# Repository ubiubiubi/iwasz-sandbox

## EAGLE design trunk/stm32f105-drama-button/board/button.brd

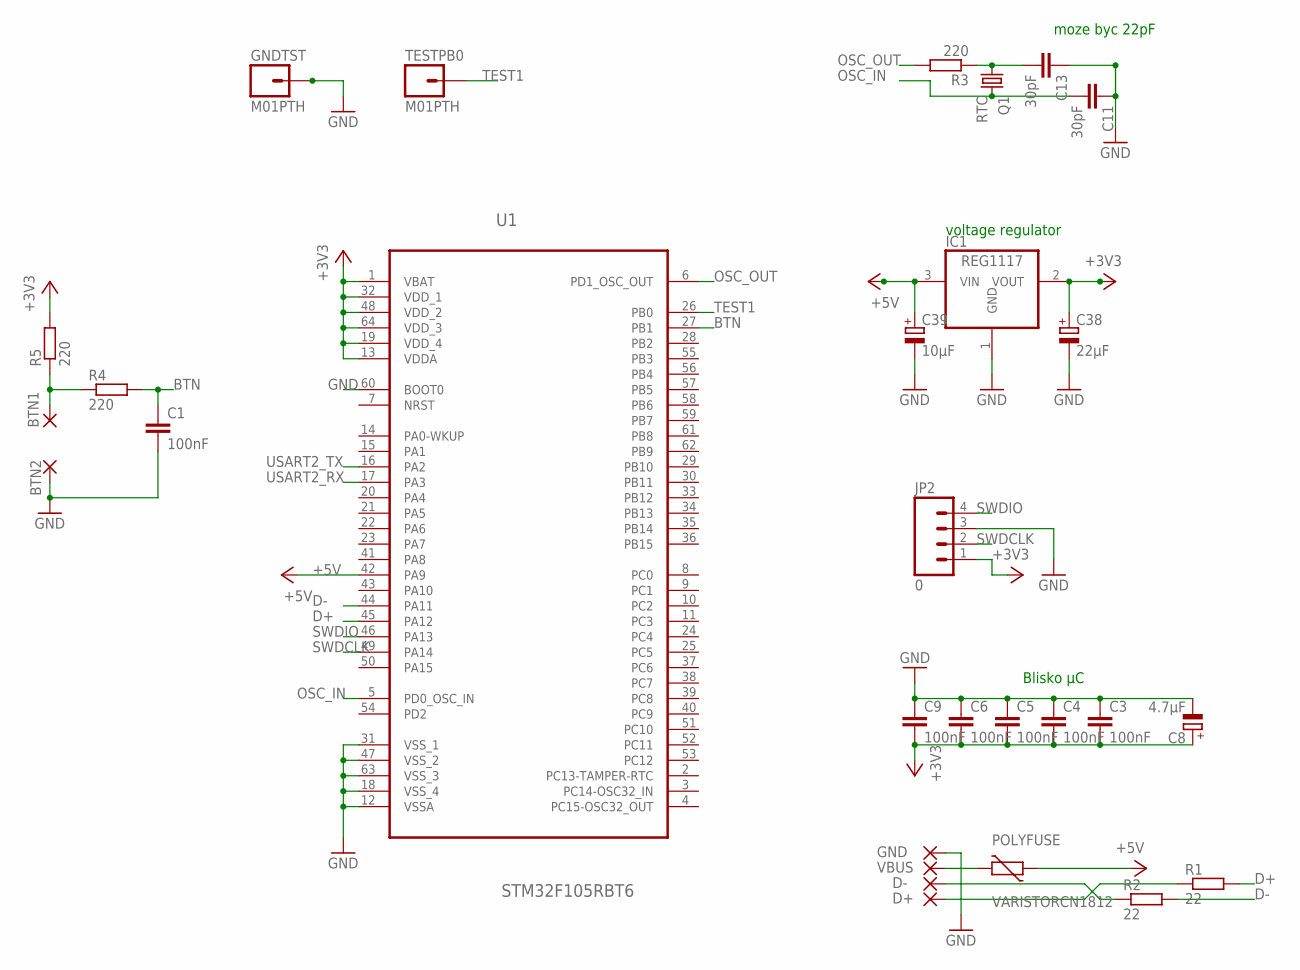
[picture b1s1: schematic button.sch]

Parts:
BTN1, BTN2: 1,6/0,8
C1, C3, C4, C5, C6, C9: 100nF; C0603
C8: 4.7µF; A/3216-18R
C11, C13: 30pF; C0603
C38: 22µF; B/3528-21W
C39: 10µF; B/3528-21W
D+: 1,6/0,8
D-: 1,6/0,8
GND: 1,6/0,8
GNDTST: M01PTH; 1X01
IC1: REG1117; SOT223
JP2: 0; 1X04
POLYFUSE: VARISTORCN1812; CT/CN1812
Q1: RTC; HC49/S
R1, R2: 22; R0805
R3, R4, R5: 220; R0603
TESTPB0: M01PTH; 1X01
U1: STM32F105RBT6; QFP50P1200X1200X160-64N
VBUS: 1,6/0,8

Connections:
+3V3: C3.2, C4.2, C5.2, C6.2, C8.+, C9.2, C38.+, IC1.2 (VOUT), JP2.1, R5.2, U1.1 (VBAT), U1.13 (VDDA), U1.19 (VDD_4), U1.32 (VDD_1), U1.48 (VDD_2), U1.64 (VDD_3)
+5V: C39.+, IC1.3 (VIN), POLYFUSE.1, U1.42 (PA9)
BTN: C1.1, R4.2, U1.27 (PB1)
D+: R1.2, U1.45 (PA12)
D-: R2.2, U1.44 (PA11)
GND: BTN2.1, C1.2, C3.1, C4.1, C5.1, C6.1, C8.-, C9.1, C11.1, C13.1, C38.-, C39.-, GND.1, GNDTST.1, IC1.1 (GND), JP2.3, U1.12 (VSSA), U1.18 (VSS_4), U1.31 (VSS_1), U1.47 (VSS_2), U1.60 (BOOT0), U1.63 (VSS_3)
unnamed: C13.2, Q1.1, R3.1
unnamed: BTN1.1, R4.1, R5.1
unnamed: D+.1, R1.1
unnamed: D-.1, R2.1
unnamed: POLYFUSE.2, VBUS.1
OSC_IN: C11.2, Q1.2, U1.5 (PD0_OSC_IN)
OSC_OUT: R3.2, U1.6 (PD1_OSC_OUT)
SWDCLK: JP2.2, U1.49 (PA14)
SWDIO: JP2.4, U1.46 (PA13)
TEST1: TESTPB0.1, U1.26 (PB0)
USART2_RX: U1.17 (PA3)
USART2_TX: U1.16 (PA2)

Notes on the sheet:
voltage regulator
Blisko µC
moze byc 22pF

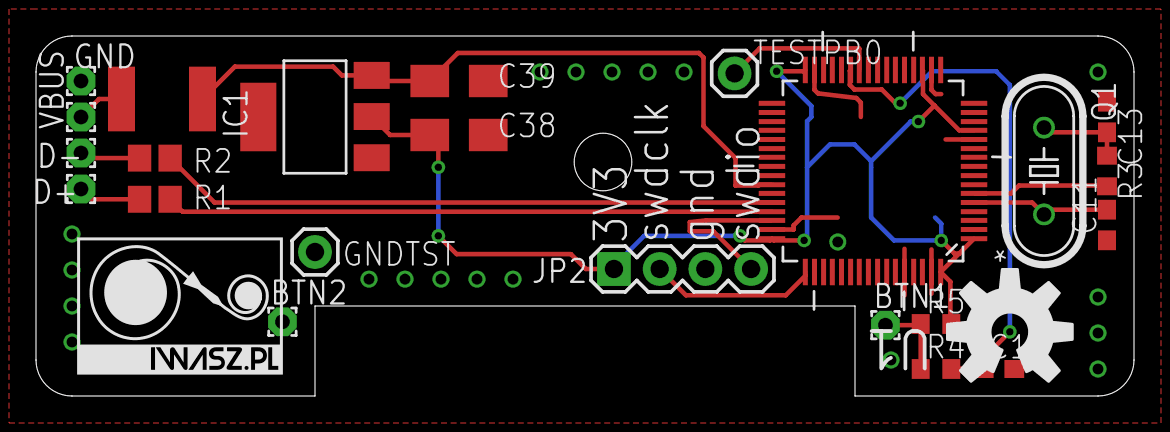
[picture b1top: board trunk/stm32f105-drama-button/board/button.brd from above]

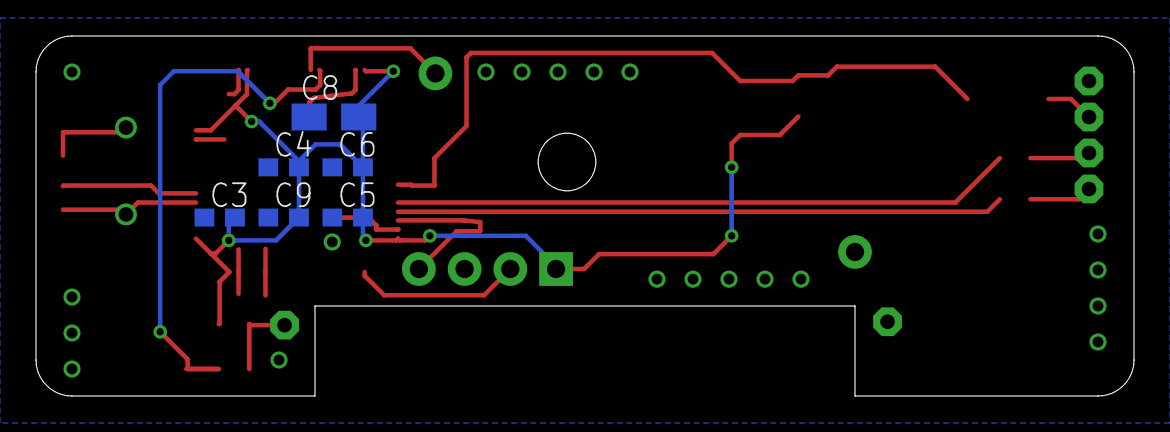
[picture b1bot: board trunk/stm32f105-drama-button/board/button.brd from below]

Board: 2 copper layers, 61.0 x 20.0 mm, 31 parts (6 on the bottom side), 16 nets.

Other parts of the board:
U$1: LOGO-TINY
U$4: OSHW-LOGO-L

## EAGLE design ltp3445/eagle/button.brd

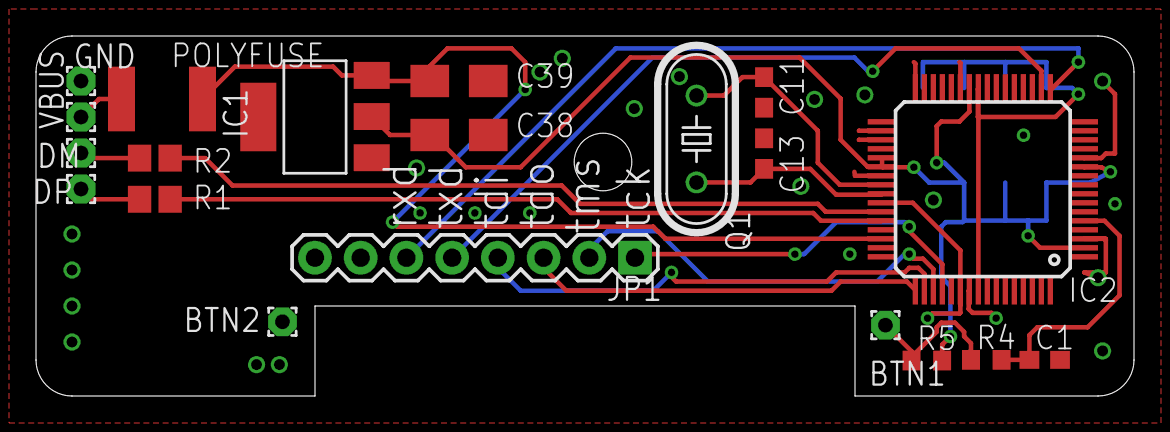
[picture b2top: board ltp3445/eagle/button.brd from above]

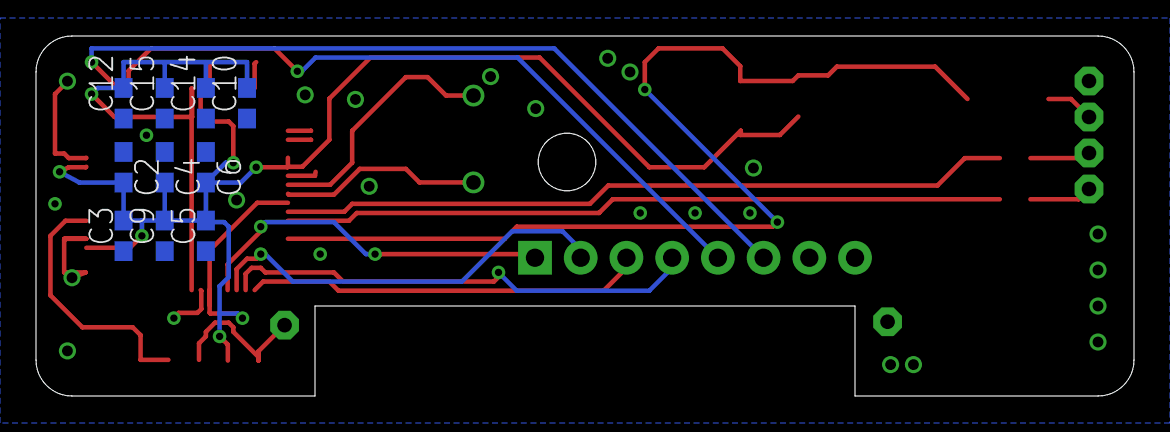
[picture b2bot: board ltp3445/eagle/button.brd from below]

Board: 2 copper layers, 61.0 x 20.0 mm, 30 parts (10 on the bottom side), 19 nets.

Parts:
BTN1, BTN2: 1,6/0,8
C1, C4, C6, C14, C15: 100nF; C0603
C2, C12: 1µF; C0603
C3, C5, C9: 10nF; C0603
C10: 2.2µF; C0603
C11, C13: 10pF; C0603
C38: 22µF; B/3528-21W
C39: 10µF; B/3528-21W
DM: 1,6/0,8
DP: 1,6/0,8
GND: 1,6/0,8
IC1: REG1117; SOT223
IC2: TM4C123[7,G]XXPM; PM_S-PQFP-G64
JP1: 1X08
POLYFUSE: VARISTORCN1812; CT/CN1812
Q1: RTC; HC49/S
R1, R2: 22; R0805
R4, R5: 220; R0603
VBUS: 5V; 1,6/0,8

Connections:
+3V3: C2.2, C3.2, C4.2, C5.2, C6.2, C9.2, C38.+, IC1.2, IC2.2, IC2.11, IC2.26, IC2.37, IC2.38, IC2.42, IC2.54, R5.2
+5V: C39.+, IC1.3, IC2.46, POLYFUSE.1
BTN: C1.1, IC2.5, R4.2
D+: IC2.44, R1.2
D-: IC2.43, R2.2
GND: BTN2.1, C1.2, C2.1, C3.1, C4.1, C5.1, C6.1, C9.1, C10.1, C11.1, C12.1, C13.1, C14.1, C15.1, C38.-, C39.-, GND.1, IC1.1, IC2.3, IC2.12, IC2.27, IC2.32, IC2.34, IC2.35, IC2.39, IC2.55, JP1.7, JP1.8
unnamed: BTN1.1, R4.1, R5.1
unnamed: DP.1, R1.1
unnamed: DM.1, R2.1
unnamed: POLYFUSE.2, VBUS.1
OSC0: C11.2, IC2.40, Q1.2
OSC1: C13.2, IC2.41, Q1.1
RXD: IC2.17, JP1.6
TCK: IC2.52, JP1.1
TDI: IC2.50, JP1.4
TDO: IC2.49, JP1.3
TMS: IC2.51, JP1.2
TXD: IC2.18, JP1.5
VDDC: C10.2, C12.2, C14.2, C15.2, IC2.25, IC2.56

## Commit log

2013-05-27 fgdyhhgn
2013-06-11 Share project "raspberry-first" into "https://iwasz-sandbox.googlecode.com/svn"
2013-06-11 first
2013-07-03 Share project "test05-hello-concurrency" into "https://iwasz-sandbox.googlecode.com/svn"
2013-07-03 hello concurrency
2013-07-21 Share project "blinky" into "https://iwasz-sandbox.googlecode.com/svn"
2013-07-21 Share project "stm32-cmake-test" into "https://iwasz-sandbox.googlecode.com/svn"
2013-07-21 test mediwaiki formatting
2013-08-02 Share project "stm32-test2" into "https://iwasz-sandbox.googlecode.com/svn"
2013-09-10 Share project "i2c-test" into "https://iwasz-sandbox.googlecode.com/svn"
2013-09-13 move
2013-09-13 trash
2013-09-17 I²C, USART, NewLib and gyro connected to I²C works. Nice output in minicom.
2013-09-27 test usb
2013-09-27 3rdparty libraries added. Those are : stdperiph, usbdev, usbhost, usbotg and CMSIS
2013-09-27 Cleared, prepared for further development
2013-09-27 Ignores and USART cfg for printf - still clear and waiting
2013-09-27 usb_conf.h added
2013-10-01 usb_bsp.c added
2013-10-01 usbd_conf.h added
2013-10-01 Few files added
2013-10-01 Libraries updated
2013-10-01 /stm32fxxx_it.c added
2013-10-01 src/system_stm32f4xx.c configured (in fact it was copied from Demonstration app) and that was finally it. This modification made app work.
2013-10-02 Code documentation imporved
2013-10-03 Documentation improvements
2013-10-04 New project USB vendor specific class test
2013-10-04 Documentation ignorea and my vendor specific class. The beginning.
2013-10-05 New project
2013-10-05 Configuration
2013-10-05 WIP sketch of USB driver program
2013-10-09 WIP - not working at the moment
2013-10-10 New interface added
2013-10-10 At last! This freaking isochronous transfer works. Alleluja
2013-10-10 adfsd
2013-10-11 rollback of last changes. Those changes were ported to usb-vendor-specific project
2013-10-13 Tests
2013-10-17 NVIC + EXTI wip
2013-10-18 Little success
2013-10-23 32 inputs
2013-10-24 UI changes
2013-11-06 Isochronous transfers changed to interrupt due to uncertanity that STM32-USB-OTG can handle isochronous at all. Probably a bug in the lib. Changed quadrature signal counting
2013-11-06 Layout improvements
2013-12-17 https://iwasz-sandbox.googlecode.com/svn/trunk/stm32-sdio-tests init
2013-12-29 Project initial commit
2013-12-30 Cleanup
2013-12-30 Device (keyboard) recognized by system. No keypress though
2014-01-01 Keypress A working
2014-01-02 Repository name change
2014-01-02 Drama button for stmf105
2014-01-02 Changin µC to F105
2014-01-02 Porting from F407 to F105
2014-01-05 Play pause implementred instead of dummy "a" button
2014-01-05 New CMSIS added. Status : messed up. Not usable :( The device resets few times, then dies
2014-01-05 Board schematics added
2014-01-06 USART1 broken, but SDIO seems to work
2014-01-06 Fixed quadrature encoding bug. Added LED status
2014-01-06 Set to zero added and negative numbers added
2014-01-06 Set to zero added (control transfer request)
2014-01-07 Theme
2014-01-07 USART still not working
2014-01-08 Tried to fix transfer stall
2014-01-10 It works.
2014-01-10 After few bugs finally I got it working.
2014-01-11 Initial commit, a test project
2014-01-12 Wrote forst test, but it didn\t work
2014-01-12 Initial release
2014-01-13 DMA OK, two transfers
2014-01-20 DB access
2014-03-15 New project test css + gtk loader program
2014-04-18 Share project "tiva-usb-test" into "https://iwasz-sandbox.googlecode.com/svn"
2014-04-18 CMake blink project OK
2014-04-24 Copy
2014-04-27 To ma być po mojemu z 'startfile'
2014-04-29 Działa jak klawisz "a".
2014-04-29 W tym komicie działa klawisz "mute", ale kernel zgłasza warningi podczas enumeracji urządzenia.
2014-05-11 "a" key working
2014-05-11 Both interfaces are working, but the "multimedia" one is malfunctioning
2014-05-12 Any key project started. This is a host app.
2014-05-12 Works!
2014-05-15 sdl;j
2014-05-26 Reflow oven project start
2014-05-26 Thermocuple K works. Readings via USART.
2014-06-09 eagle files as promissed on site
2014-06-30 Initial commit.
2014-07-08 Oscillator frequency was misconfigured. Rised from 8 to 16MHz.
2014-07-08 Clock Divider 2.5
2014-07-16 franek prints himself
2014-09-05 Initial. Copied from ltp3445 project.
2014-09-09 Template works OK. Blinks as it should
2014-12-09 ignores and missed changes from the past
2015-04-15 Migrating wiki contents from Google Code

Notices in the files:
parts and their libraries:
SparkFun-Connectors: Licensing: CC v3.0 Share-Alike You are welcome to use this library for commercial purposes.
